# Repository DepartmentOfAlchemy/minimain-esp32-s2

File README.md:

## MiniMain ESP32-S2

PCB files for the MiniMain ESP32-S2 in an Adafruit Feather compatible format.

### Description

This Feather-shaped main board contains an ESP32-S2 for the main microcontroller. It contains 4 MB of flash + 2 MB of PSRAM along with native USB.

This board is designed for use in haunted attraction props as it includes an optoisolated input that allows it to be triggered by another prop controller operating at 12V. This is where the MiniMain deviates from a standard Adafruit Feather: it does not include support for battery operation. (There is also one additional pin broken out in standard 2.54mm pitch format designed for a servo.)

### License

Inspired by [Adafruit Feather ESP32-S2](https://github.com/adafruit/Adafruit-Feather-ESP32-S2-PCB). Adafruit invests time and resources providing this open source design, please support Adafruit and open-source hardware by purchasing products from [Adafruit](https://www.adafruit.com)!

Adafruit Feather ESP32-S2 designed by Limor Fried/Ladyada for Adafruit Industries.

MiniMain ESP32-S2 designed by Jesse Peterson/cubeinhabitant.

Creative Commons Attribution/Share-Alike

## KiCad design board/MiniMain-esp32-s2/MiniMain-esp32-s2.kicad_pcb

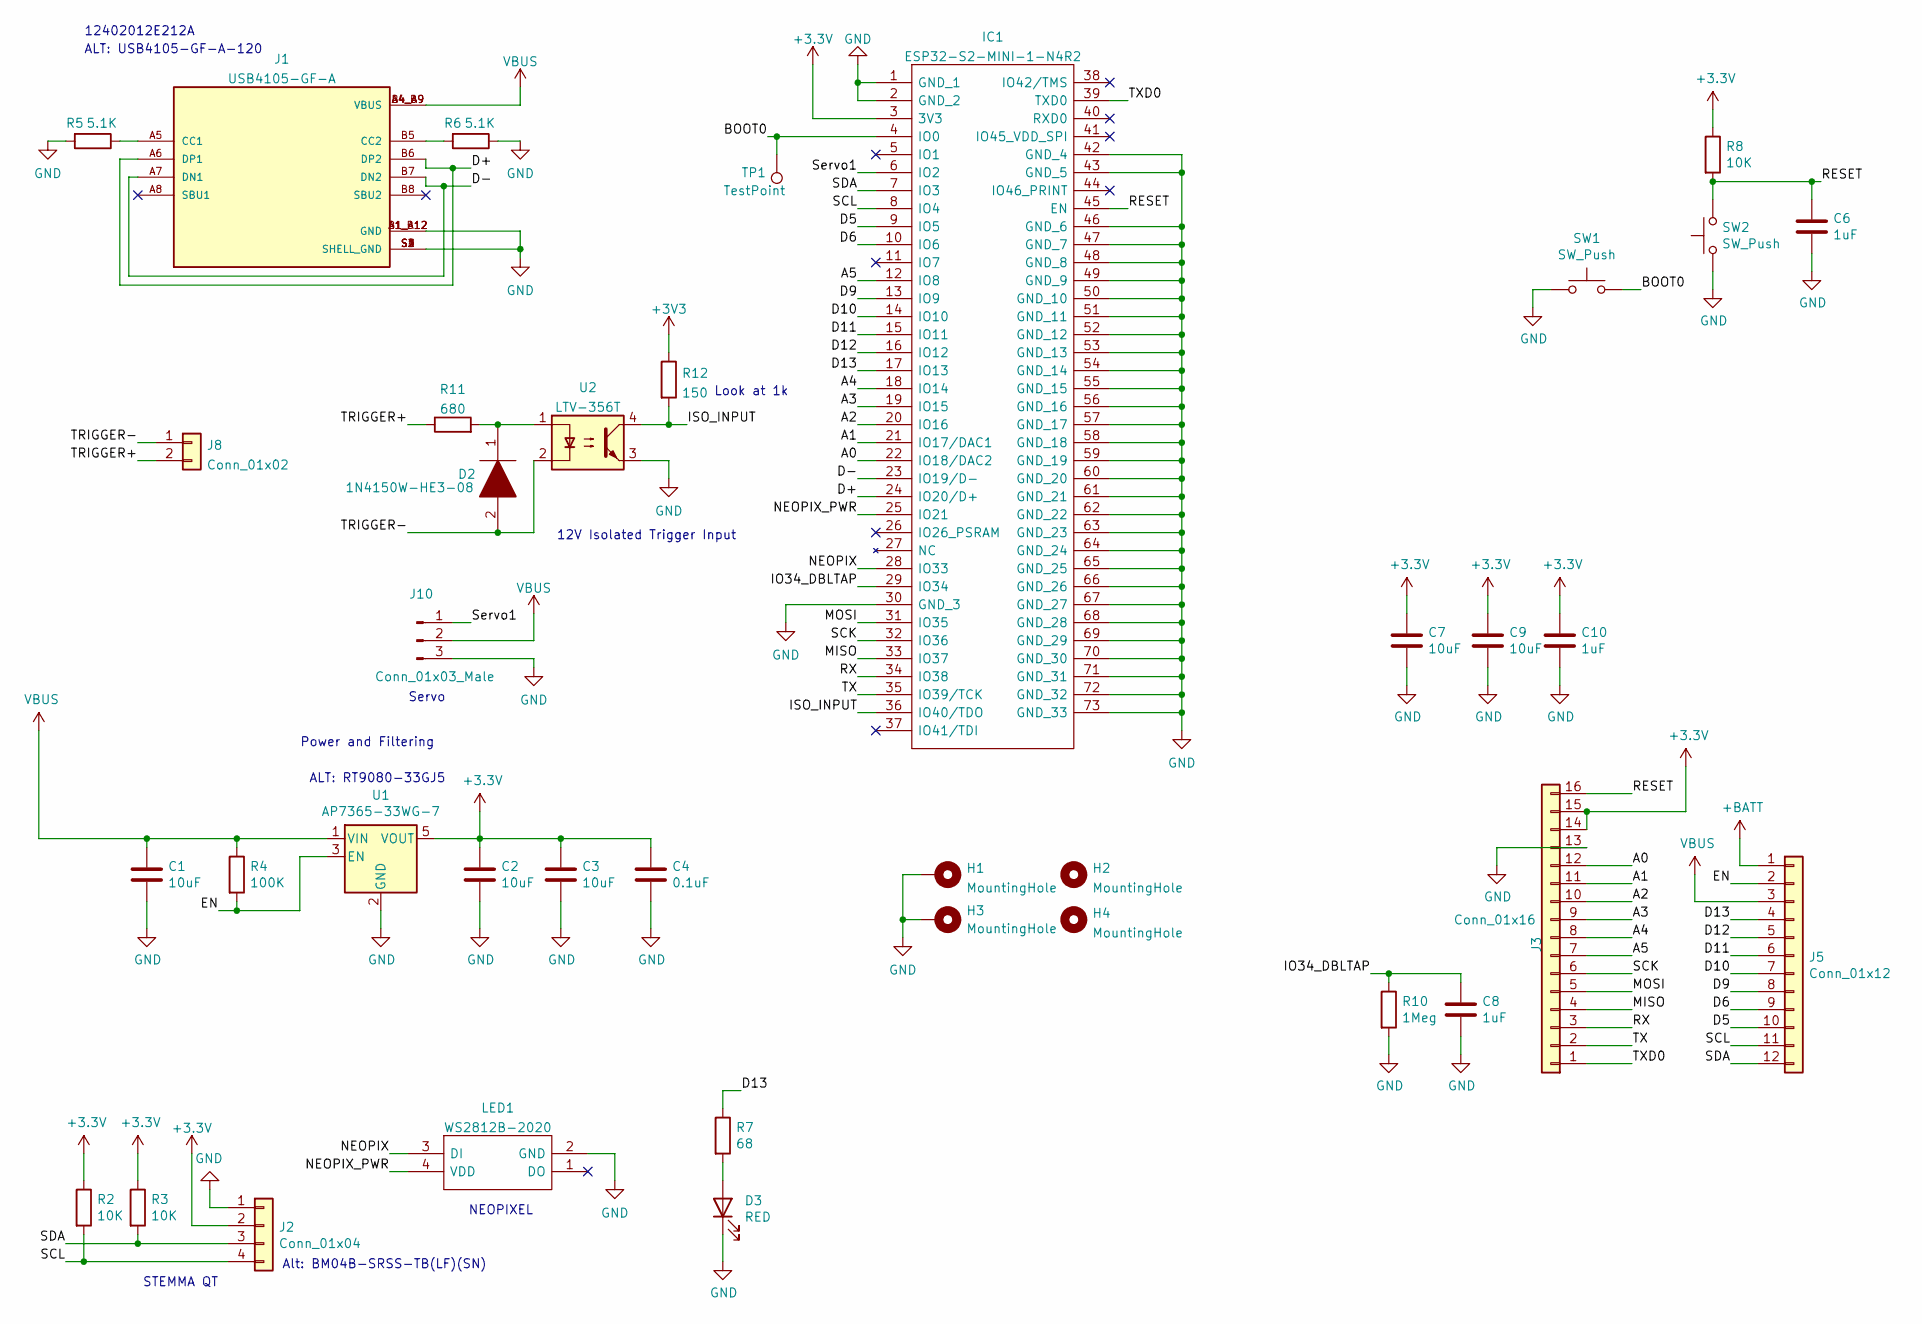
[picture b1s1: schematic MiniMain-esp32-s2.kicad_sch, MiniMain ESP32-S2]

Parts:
C1, C2, C3, C9: 10uF; C_0603_1608Metric
C4: 0.1uF; C_0603_1608Metric
C6, C8, C10: 1uF; C_0603_1608Metric
C7: 10uF; C_0402_1005Metric
D2: 1N4150W-HE3-08; D_SOD-123; Manufacturer_Part_Number S1GTR
D3: RED; LED_0603_1608Metric
H1, H3: MountingHole; MountingHole_2.7mm_M2.5_ISO14580_Pad
H2, H4: MountingHole; MountingHole_2.7mm_M2.5_ISO14580
IC1: ESP32-S2-MINI-1-N4R2; ESP32S2MINI1N4R2; Manufacturer_Part_Number ESP32-S2-MINI-1-N4R2; Mouser Part Number 356-ESP32S2MINI1N4R2
J1: USB4105-GF-A; GCT_USB4105-GF-A; PARTREV A3
J2: Conn_01x04; JST_SH_BM04B-SRSS-TB_1x04-1MP_P1.00mm_Vertical
J3: Conn_01x16; PinHeaderPlain_1x16_P2.54mm_Vertical
J5: Conn_01x12; PinHeaderPlain_1x12_P2.54mm_Vertical
J8: Conn_01x02; OSTVN02A150
J10: Conn_01x03_Male; PinHeader_1x03_P2.54mm_Vertical
LED1: WS2812B-2020; WS2812B2020; Manufacturer_Part_Number WS2812B-2020
R2, R3, R8: 10K; R_0603_1608Metric
R4: 100K; R_0603_1608Metric
R5, R6: 5.1K; R_0603_1608Metric
R7: 68; R_0603_1608Metric
R10: 1Meg; R_0603_1608Metric
R11: 680; R_0603_1608Metric
R12: 150; R_0603_1608Metric
SW1, SW2: SW_Push; SW_Push_1P1T_NO_CK_KMR2
TP1: TestPoint; TestPoint_Pad_D1.5mm
U1: AP7365-33WG-7; SOT-23-5
U2: LTV-356T; SO-4_4.4x3.6mm_P2.54mm

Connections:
+BATT: J5.1
/A0: IC1.22 (IO18/DAC2), J3.12
/A1: IC1.21 (IO17/DAC1), J3.11
/A2: IC1.20 (IO16), J3.10
/A3: IC1.19 (IO15), J3.9
/A4: IC1.18 (IO14), J3.8
/A5: IC1.12 (IO8), J3.7
/BOOT0: IC1.4 (IO0), SW1.2, TP1.1
/D5: IC1.9 (IO5), J5.10
/D6: IC1.10 (IO6), J5.9
/D9: IC1.13 (IO9), J5.8
/D10: IC1.14 (IO10), J5.7
/D11: IC1.15 (IO11), J5.6
/D12: IC1.16 (IO12), J5.5
/D13: IC1.17 (IO13), J5.4, R7.1
/D+: IC1.24 (IO20/D+), J1.A6 (DP1), J1.B6 (DP2)
/D-: IC1.23 (IO19/D-), J1.A7 (DN1), J1.B7 (DN2)
/EN: J5.2, R4.2, U1.3 (EN)
/IO34_DBLTAP: C8.1, IC1.29 (IO34), R10.1
/ISO_INPUT: IC1.36 (IO40/TDO), R12.2, U2.4
/MISO: IC1.33 (IO37), J3.4
/MOSI: IC1.31 (IO35), J3.5
/NEOPIX: IC1.28 (IO33), LED1.3 (DI)
/NEOPIX_PWR: IC1.25 (IO21), LED1.4 (VDD)
/RESET: C6.1, IC1.45 (EN), J3.16, R8.2, SW2.2
/RX: IC1.34 (IO38), J3.3
/SCK: IC1.32 (IO36), J3.6
/SCL: IC1.8 (IO4), J2.4, J5.11, R2.2
/SDA: IC1.7 (IO3), J2.3, J5.12, R3.2
/Servo1: IC1.6 (IO2), J10.1
/TRIGGER+: J8.2, R11.1
/TRIGGER-: D2.2, J8.1, U2.2
/TX: IC1.35 (IO39/TCK), J3.2
/TXD0: IC1.39 (TXD0), J3.1
GND: C1.2, C2.2, C3.2, C4.2, C6.2, C7.2, C8.2, C9.2, C10.2, D3.1 (K), H1.1, H3.1, IC1.1 (GND_1), IC1.2 (GND_2), IC1.30 (GND_3), IC1.42 (GND_4), IC1.43 (GND_5), IC1.46 (GND_6), IC1.47 (GND_7), IC1.48 (GND_8), IC1.49 (GND_9), IC1.50 (GND_10), IC1.51 (GND_11), IC1.52 (GND_12), IC1.53 (GND_13), IC1.54 (GND_14), IC1.55 (GND_15), IC1.56 (GND_16), IC1.57 (GND_17), IC1.58 (GND_18), IC1.59 (GND_19), IC1.60 (GND_20), IC1.61 (GND_21), IC1.62 (GND_22), IC1.63 (GND_23), IC1.64 (GND_24), IC1.65 (GND_25), IC1.66 (GND_26), IC1.67 (GND_27), IC1.68 (GND_28), IC1.69 (GND_29), IC1.70 (GND_30), IC1.71 (GND_31), IC1.72 (GND_32), IC1.73 (GND_33), J1.A1_B12 (GND), J1.B1_A12 (GND), J1.S1 (SHELL_GND), J1.S2 (SHELL_GND), J1.S3 (SHELL_GND), J1.S4 (SHELL_GND), J2.1, J3.13, J10.3, LED1.2 (GND), R5.2, R6.1, R10.2, SW1.1, SW2.1, U1.2 (GND), U2.3
unnamed: D2.1, R11.2, U2.1
unnamed: D3.2 (A), R7.2
unnamed: J1.A5 (CC1), R5.1
unnamed: J1.B5 (CC2), R6.2
VBUS: C1.1, J1.A4_B9 (VBUS), J1.B4_A9 (VBUS), J5.3, J10.2, R4.1, U1.1 (VIN)

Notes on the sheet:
Alt: BM04B-SRSS-TB(LF)(SN)
ALT: RT9080-33GJ5
NEOPIXEL
12402012E212A
12V Isolated Trigger Input
ALT: USB4105-GF-A-120
STEMMA QT
Look at 1k
Servo
Power and Filtering

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
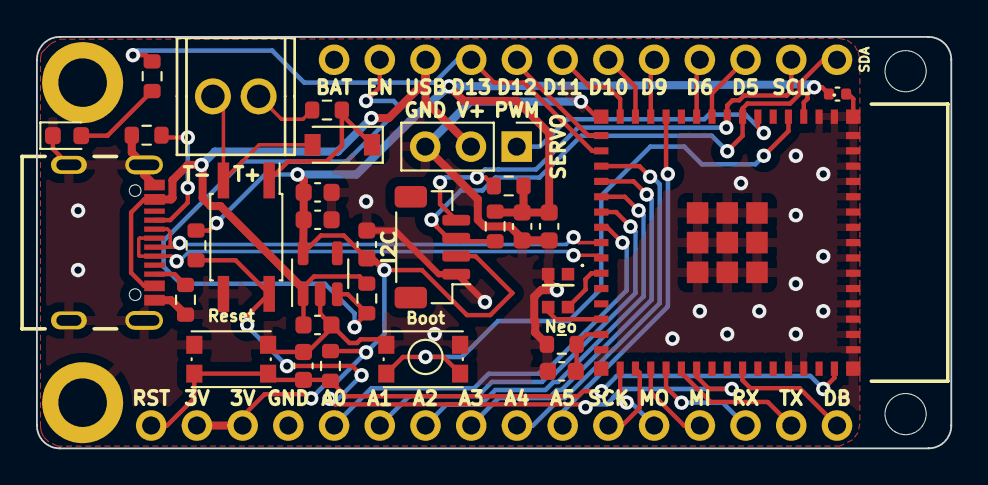
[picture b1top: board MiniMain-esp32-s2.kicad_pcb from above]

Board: 2 copper layers, 50.8 x 22.9 mm, 38 parts (0 on the bottom side), 40 nets.

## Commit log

2021-12-30 Initial board commit.
2021-12-31 Added support for turning power off on the "Stemma QT" port like in the Adafruit esp32-s2 feather.
2022-02-13 Updated the gitignore with the KiCad specific values.
2022-02-13 Board layout complete with silkscreen done.
2022-02-13 Fix a few unconnected nets. DRC now shows nothing unconnected.
2022-02-23 Revealed the values of the components in the front fab so that I can see where each component goes for board population.
2022-02-26 Minor update for the fabrication layer for part location.
2022-04-03 Renamed to more accurately reflect that this is for an ESP32-S2. Also added the revision of 0.1.
2022-04-17 Rev 2: Change Stemma QT compatible port from transistor controlled power to just +3.3V. Remove copper pour under the ESP32-S2 antenna. Perhaps look at changing the isolated input pull-up from 150 ohm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
2022-04-17 Rev 2: PCB changes after DRC. (Even though I didn't change anything.)
2022-05-08 License added. Also added photo of Rev 2 prototype.
2022-05-08 License added. Also added photo of Rev 2 prototype. (#1)
2022-05-08 Updated README to include MiniMain's feature goals.
2022-05-08 Update README.md
    Fix a couple spelling issues.
